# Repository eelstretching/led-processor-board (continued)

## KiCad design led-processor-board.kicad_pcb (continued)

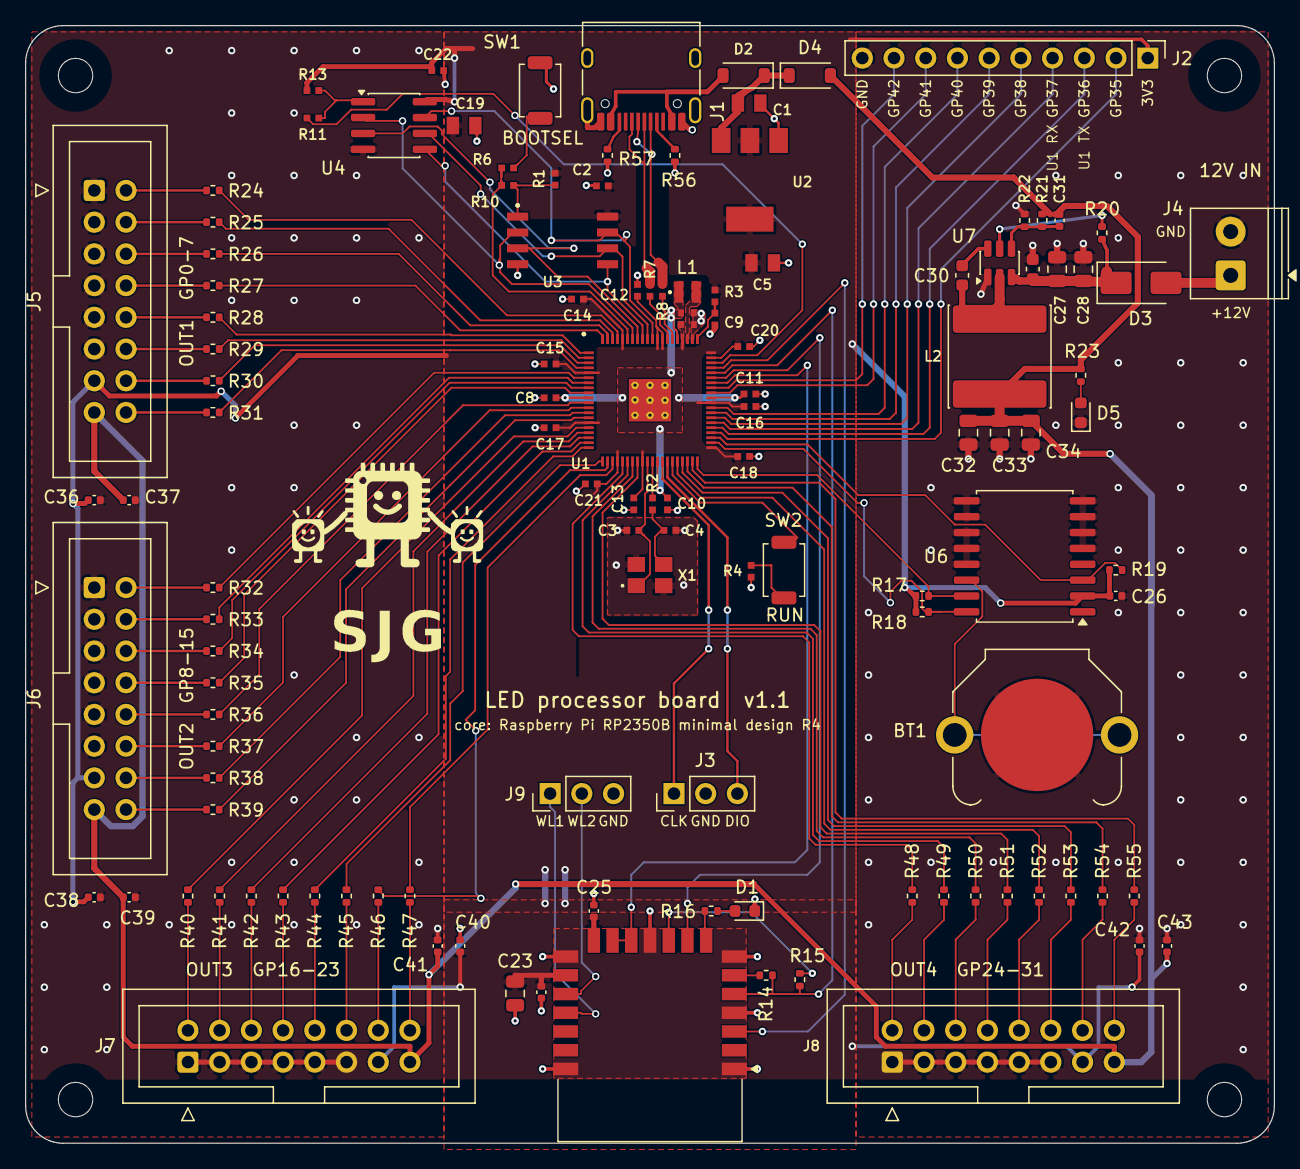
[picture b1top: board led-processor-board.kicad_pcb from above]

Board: 2 copper layers, 100.0 x 89.5 mm, 128 parts (0 on the bottom side), 124 nets.

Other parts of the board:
G1: SJG_BigBrother

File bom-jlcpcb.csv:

Comment,Designator,Footprint,LCSC,Manufacturer PN,Qty,Note
CR1220,BT1,BatteryHolder_Keystone_3001_1x12mm,,3001,1,"Not at LCSC: Keystone 3001 (Digi-Key 36-3001-ND), hand-solder"
10u,"C1,C5,C19",generic_capc2012x125,C15850,CL21A106KAYNNNE,3,
100n,"C2,C8,C10,C11,C12,C13,C14,C15,C16,C17,C18,C20,C21,C22",generic_capc1005x50,C1525,CL05B104KO5NNNC,14,
15p,"C3,C4",generic_capc1005x50,C1548,0402CG150J500NT,2,
4.7u,"C6,C7",generic_capc1005x50_wide,C23733,CL05A475MP5NRNC,2,
4.7u,C9,generic_capc1005x50,C23733,CL05A475MP5NRNC,1,
10u,C23,C_0805_2012Metric,C15850,CL21A106KAYNNNE,1,
100n,"C24,C25,C36,C37,C38,C39,C40,C41,C42,C43",C_0402_1005Metric,C1525,CL05B104KO5NNNC,10,
1u,C26,C_0402_1005Metric,C52923,CL05A105KA5NQNC,1,
10u,"C27,C28",C_0805_2012Metric,C440198,CL21A106KBYNNNE,2,
100n,"C29,C30",C_0603_1608Metric,C14663,CC0603KRX7R9BB104,2,
75p,C31,C_0402_1005Metric,C37809,0402CG750J500NT,1,
22u,"C32,C33,C34",C_0805_2012Metric,C45783,CL21A226MAQNNNE,3,
Green,"D1,D5",LED_0603_1608Metric,C72043,19-217/GHC-YR1S2/3T,2,
B5819W,"D2,D4",D_SOD-123,C8598,B5819W SL,2,
SS34,D3,D_SMA,C8678,SS34,1,
USB-C,J1,USB_C_Receptacle_HRO_TYPE-C-31-M-12,C165948,TYPE-C-31-M-12,1,
SPARE,J2,PinHeader_1x10_P2.54mm_Vertical,,1x10 2.54 mm pin header,1,Through-hole: hand-solder
SWD,J3,PinHeader_1x03_P2.54mm_Vertical,,1x3 2.54 mm pin header,1,Through-hole: hand-solder
12V IN,J4,"TerminalBlock_Phoenix_PT-1,5-2-3.5-H_1x02_P3.50mm_Horizontal",C695629,DB301V-3.5-2P-GN-S,1,Through-hole
OUT1,J5,IDC-Header_2x08_P2.54mm_Vertical,,Box header 2x08 2.54 mm,1,Through-hole: hand-solder (same shroud as the output boards)
OUT2,J6,IDC-Header_2x08_P2.54mm_Vertical,,Box header 2x08 2.54 mm,1,Through-hole: hand-solder (same shroud as the output boards)
OUT3,J7,IDC-Header_2x08_P2.54mm_Vertical,,Box header 2x08 2.54 mm,1,Through-hole: hand-solder (same shroud as the output boards)
OUT4,J8,IDC-Header_2x08_P2.54mm_Vertical,,Box header 2x08 2.54 mm,1,Through-hole: hand-solder (same shroud as the output boards)
WL_GPIO,J9,PinHeader_1x03_P2.54mm_Vertical,,1x3 2.54 mm pin header,1,Through-hole: hand-solder
3.3u,L1,abracon_aota-b201610s3r3-101-t,C42411119,AOTA-B201610S3R3-101-T,1,
15u,L2,L_Sunlord_SWPA8040S,C16853,SWPA8040S150MT,1,
1k,"R2,R4,R6",generic_resc1005x35,C11702,0402WGF1001TCE,3,
33,R3,generic_resc1005x35,C25105,0402WGF330JTCE,1,
27,"R7,R8",generic_resc1005x35,C25100,0402WGF270JTCE,2,
0,"R10,R11",generic_resc1005x35,C17168,0402WGF0000TCE,2,
10k,R13,generic_resc1005x35,C25744,0402WGF1002TCE,1,
470,R14,R_0402_1005Metric,C25117,0402WGF4700TCE,1,
10k,"R15,R17,R18,R19",R_0402_1005Metric,C25744,0402WGF1002TCE,4,
1k,"R16,R23",R_0402_1005Metric,C11702,0402WGF1001TCE,2,
510k,R20,R_0402_1005Metric,C11616,0402WGF5103TCE,1,
100k,R21,R_0402_1005Metric,C25741,0402WGF1003TCE,1,
13.3k,R22,R_0402_1005Metric,C122547,0402WGF1332TCE,1,
33,"R24,R25,R26,R27,R28,R29,R30,R31,R32,R33,R34,R35,R36,R37,R38,R39,R40,R41,R42,R43,R44,R45,R46,R47,R48,R49,R50,R51,R52,R53,R54,R55",R_0402_1005Metric,C25105,0402WGF330JTCE,32,
5.1k,"R56,R57",R_0402_1005Metric,C25905,0402WGF5101TCE,2,
TS-1088R-02526,"SW1,SW2",SW_SPST_TS-1088-xR025,C455281,TS-1088R-02526,2,
RP2350B,U1,rpi_rp2350b_vias,C42415655,RP2350B,1,
NCP1117ST33T3G,U2,onsemi_ncp1117st33t3g,C26537,NCP1117ST33T3G,1,
W25Q128JVSIQ,U3,generic_soic127p790x195-8,C97521,W25Q128JVSIQ,1,
APS6404L-3SQR-SN,U4,SOIC-8_3.9x4.9mm_P1.27mm,C5333729,APS6404L-3SQR-SN,1,
RM2,U5,RPi_RM2,,SC1169 (RMC20452T),1,Not at LCSC: buy RM2 (Raspberry Pi SC1169) and hand-solder
DS3231SN,U6,SOIC-16W_7.5x10.3mm_P1.27mm,C9866,DS3231SN#T&R,1,
TPS54202H,U7,SOT-23-6,C527684,TPS54202HDDCR,1,
12MHz,X1,generic_xtalcc320x250x80-4,C20625731,ABM8-272-T3,1,

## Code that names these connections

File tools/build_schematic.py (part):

"""Build the LED processor board schematic from the RP2350B-RM2 reference.

Root sheet: the reference (RP2350B, flash, PSRAM, RM2, USB, crystal, buttons) with the
J2/J3 single-row headers replaced by the DS3231 RTC, a spare-GPIO header and an SWD
header. GPIO0-31 become global labels and go to the Outputs sheet (four 16-pin ribbon
shrouds, pinout as the output boards). Power sheet: 12 V in -> TPS54202H buck -> +5 V
(ribbons) -> B5819W -> VSYS (existing NCP1117 3.3 V regulator).
"""
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
walk(ref)
for e in sx.findall(ref, 'text'):
    if e[1].startswith('VSYS is also J3 pin 2'):
        e[1] = ('VSYS comes from the 12 V input: buck to +5V, then\n'
                'D4 (Power sheet). D2 keeps that 5 V off the USB port;\n'
                'USB alone runs it through D2 (no +5V on ribbons).')

# 4. new root content: RTC, spare GPIO header, SWD header
sh = root
U6 = sh.symbol('Timer_RTC:DS3231M', SYM['Timer_RTC:DS3231M'], 'U6', 'DS3231SN', (370.84, 142.24),
               fields=part('DS3231SN#T&R', 'C9866', 'Analog Devices (Maxim)',
                           'RTC with TCXO and crystal, I2C, SOIC-16W (same as universal-strip-controller U9)',
                           'Package_SO:SOIC-16W_7.5x10.3mm_P1.27mm'),
               ref_at=(374.65, 128.27), val_at=(374.65, 130.81))
sh.wire(U6[16], (350.52, U6[16][1])); sh.label('GPIO33', (350.52, U6[16][1]), 180)
sh.wire(U6[15], (350.52, U6[15][1])); sh.label('GPIO32', (350.52, U6[15][1]), 180)
sh.nc(U6[4]); sh.nc(U6[1])
sh.wire(U6[3], (391.16, U6[3][1])); sh.label('GPIO34', (391.16, U6[3][1]), 0)
sh.wire(U6[2], (U6[2][0], 127.0)); pwr(sh, '+3V3', (U6[2][0], 127.0))
gnd(sh, U6[13])
# battery: VBAT up and over to BT1
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C26 = C(sh, 'C26', '1u', (345.44, 124.46), ref_at=(347.98, 123.19), val_at=(347.98, 125.73))
pwr(sh, '+3V3', C26[1]); gnd(sh, C26[2])
# pull-ups on SDA, SCL, INT
for k, (refd, net) in enumerate([('R17', 'GPIO32'), ('R18', 'GPIO33'), ('R19', 'GPIO34')]):
    x = 345.44 + 7.62 * k
    rr = R(sh, refd, '10k', (x, 163.83), ref_at=(x + 1.905, 162.56), val_at=(x + 1.905, 165.1))
    pwr(sh, '+3V3', rr[1])
    sh.wire(rr[2], (x, 172.72)); sh.label(net, (x, 172.72), 270)
sh.text('RTC: the DS3231 circuit from universal-strip-controller (U9), on I2C0:\n'
        'SDA = GPIO32, SCL = GPIO33, INT/SQW = GPIO34 (open drain, pulled up).\n'
        '32KHZ and RST unused. CR1220 in a Keystone 3001 holder.', (335.28, 114.3))
# spare GPIO header J2
J2 = sh.symbol('Connector_Generic:Conn_01x10', SYM['Connector_Generic:Conn_01x10'], 'J2', 'SPARE',
               (403.86, 182.88),
               fields=part('1x10 2.54 mm pin header', '', '', 'Spare GPIO35-42, 3V3, GND. Through-hole: hand-solder',
                           'Connector_PinHeader_2.54mm:PinHeader_1x10_P2.54mm_Vertical'),
               ref_at=(400.05, 166.37), val_at=(403.86, 166.37))
sh.wire(J2[1], (393.7, J2[1][1])); pwr(sh, '+3V3', (393.7, J2[1][1]))
for n, net in zip(range(2, 10), ['GPIO35', 'GPIO36', 'GPIO37', 'GPIO38', 'GPIO39', 'GPIO40_ADC0',
                                 'GPIO41_ADC1', 'GPIO42_ADC2']):
    sh.wire(J2[n], (388.62, J2[n][1])); sh.label(net, (388.62, J2[n][1]), 180)
sh.wire(J2[10], (393.7, J2[10][1])); gnd(sh, (393.7, J2[10][1]))
# SWD header J3 (Pico debug pin order)
J3 = sh.symbol('Connector_Generic:Conn_01x03', SYM['Connector_Generic:Conn_01x03'], 'J3', 'SWD',
               (403.86, 157.48),
               fields=part('1x3 2.54 mm pin header', '', '', 'SWD debug: SWCLK, GND, SWD (Pico order). Through-hole: hand-solder',
                           'Connector_PinHeader_2.54mm:PinHeader_1x03_P2.54mm_Vertical'),
               ref_at=(400.05, 149.86), val_at=(403.86, 149.86))
sh.wire(J3[1], (388.62, J3[1][1])); sh.label('SWCLK', (388.62, J3[1][1]), 180)
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pwr_n[0] += 1
sh.symbol('RPI - Power:GND', SYM['RPI - Power:GND'], '#PWR%d' % pwr_n[0], 'GND', (393.7, J3[2][1]), rot=270,
          power=True, in_bom=False, val_at=(389.89, J3[2][1] - 1.27), hide_value=True)
sh.wire(J3[3], (388.62, J3[3][1])); sh.label('SWD', (388.62, J3[3][1]), 180)
sh.text('J2: spare GPIO35-42. UART1 TX/RX = GPIO36/37,\n'
        'GPIO40-42 = ADC0-2. J3: SWD in a Pico\'s debug pin order.\n'
        'GPIO0-31 go to the four output shrouds (Outputs sheet).\n'
        'GPIO43-47 are the RM2 and the PSRAM.', (335.28, 213.36))

# 4b. USB-C receptacle in place of Pi's micro-B
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    y = oy + 2.54 + 2.54 * i
    sh.wire((ox, y), (ox - 5.08, y)); sh.label('GPIO%d' % i, (ox - 5.08, y), 180)
    sh.wire((ox + ow, y), (ox + ow + 5.08, y)); sh.label('GPIO%d' % (16 + i), (ox + ow + 5.08, y), 0)
sh.text('GPIO0-31 to the four output shrouds', (ox - 5.08, oy - 3.81))
sh.text('12 V in, 5 V buck', (355.6, 63.5), size=2.54)

# ======================================================================================
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D3 = sh.symbol('Device:D_Schottky', SYM['Device:D_Schottky'], 'D3', 'SS34', (44.45, 76.2), rot=180,
               fields=part('SS34', 'C8678', 'MDD', 'Schottky 40 V 3 A, reverse-polarity protection', 'Diode_SMD:D_SMA'),
               ref_at=(41.91, 71.12), val_at=(41.91, 73.66))
sh.wire(J4[1], D3[2]); sh.label('VIN_RAW', (33.02, 76.2), 0)
# +12V bus with taps
taps12 = [D3[1][0], 50.8, 53.34, 58.42, 66.04, 73.66, 81.28, 91.44]
for a, b in zip(taps12, taps12[1:]):
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
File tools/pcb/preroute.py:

# hand routing for the buck (exec'd by build_pcb.py after placement)
def trk(net_name, pts, w, layer=pcbnew.F_Cu):
    for (x0, y0), (x1, y1) in zip(pts, pts[1:]):
        t = pcbnew.PCB_TRACK(b)
        t.SetStart(V(x0, y0)); t.SetEnd(V(x1, y1))
        t.SetWidth(mm(w)); t.SetLayer(layer)
        t.SetNet(net(net_name))
        b.Add(t)


def via(net_name, x, y, d=0.6, drill=0.3):
    v = pcbnew.PCB_VIA(b)
    v.SetPosition(V(x, y)); v.SetWidth(mm(d)); v.SetDrill(mm(drill))
    v.SetNet(net(net_name))
    b.Add(v)


# 12 V in: J4 -> D3 -> input caps -> VIN
trk('/Power/VIN_RAW', [(146.5, 90.0), (145.9, 90.6), (141.32, 90.6)], 0.8)
trk('+12V', [(137.32, 90.6), (134.7, 90.45), (132.6, 90.45), (130.65, 90.45)], 0.8)
trk('+12V', [(130.65, 90.45), (129.6, 90.45), (128.95, 90.138)], 0.6)
# input caps' GND straight down to the bottom plane
for x, y in ((130.65, 87.6), (132.6, 87.45), (134.7, 87.45)):
    trk('GND', [(x, y), (x, y + 1.0)], 0.5)
    via('GND', x, y)
# SW node: pin 2 straight down into L2, boot cap alongside
trk('/Power/SW', [(128.0, 90.138), (128.0, 93.0)], 0.8)
trk('/Power/SW', [(125.0, 90.775), (125.0, 93.0)], 0.5)
trk('Net-(U7-BOOT)', [(127.05, 87.862), (126.3, 87.862), (125.0, 89.162), (125.0, 89.225)], 0.3)
# U7 GND: the boot cap and SW wall it in on top, so it drops to the plane
trk('GND', [(127.05, 90.138), (126.5, 91.5)], 0.4)
via('GND', 126.5, 91.5)
# EN pull-up from the 12 V riser; EN hops under the FB parts on B.Cu
trk('+12V', [(136.2, 87.11), (136.6, 88.0), (136.6, 89.9)], 0.3)
trk('Net-(U7-EN)', [(136.2, 86.09), (136.2, 85.2)], 0.25)
via('Net-(U7-EN)', 136.2, 85.2)
trk('Net-(U7-EN)', [(136.2, 85.2), (128.0, 86.3)], 0.25, pcbnew.B_Cu)
via('Net-(U7-EN)', 128.0, 86.3)
trk('Net-(U7-EN)', [(128.0, 86.3), (128.0, 87.862)], 0.25)
# FB divider right above FB
trk('/Power/FB', [(128.95, 87.862), (128.95, 86.6), (129.44, 86.11), (130.0, 86.11), (131.4, 86.11), (132.8, 86.08)], 0.25)
trk('+5V', [(131.4, 85.09), (132.8, 85.12)], 0.25)
trk('GND', [(130.0, 85.09), (129.3, 84.4)], 0.3)
via('GND', 129.3, 84.4)
# output: L2 into the three 22u, their GND to the plane
trk('+5V', [(128.0, 100.4), (128.0, 101.65)], 0.8)
trk('+5V', [(125.5, 101.65), (130.5, 101.65)], 0.8)
for x in (125.5, 128.0, 130.5):
    trk('GND', [(x, 103.55), (x, 104.7)], 0.5)
    via('GND', x, 104.7)

# USB-C, left to right: B5 CC2, A8, B6 D+, A7 D-, A6 D+, B7 D-, A5 CC1, B8, A4 VBUS (0.5 mm pitch).
# A6/B7 carry the pair down to R7/R8; B6 joins D+ round the A7 via, and A7 hops to D- on B.Cu
# (above Pi's GPIO47 trace, which runs across under here on B.Cu).
PY = 77.695
trk('/USB_D+', [(99.55, PY), (99.55, 89.25), (99.725, 89.425)], 0.15)
trk('/USB_D-', [(100.05, PY), (100.05, 79.9), (100.15, 80.3), (100.05, 80.7), (100.05, 88.35), (100.675, 88.975)], 0.15)
trk('/USB_D+', [(98.55, PY), (98.55, 78.7), (98.35, 78.9), (98.35, 79.9), (99.55, 81.1)], 0.15)
trk('/USB_D-', [(99.05, PY), (99.05, 78.42), (98.95, 79.3)], 0.15)
via('/USB_D-', 98.95, 79.3)
trk('/USB_D-', [(98.95, 79.3), (100.15, 80.3)], 0.15, pcbnew.B_Cu)
via('/USB_D-', 100.15, 80.3)
# CC pull-downs
trk('Net-(J1-CC1)', [(100.55, PY), (100.55, 78.42), (101.0, 78.87), (102.0, 79.89)], 0.2)
trk('Net-(J1-CC2)', [(97.55, PY), (97.55, 78.42), (97.1, 78.87), (96.6, 79.89)], 0.2)
for x in (102.0, 96.6):
    trk('GND', [(x, 80.91), (x, 81.8)], 0.3)
    via('GND', x, 81.8)
# VBUS: both VBUS pads up past the locating pegs, across under the receptacle, then to D2;
# D2/D4 feed VSYS at C1 and U2
trk('VBUS', [(96.85, PY), (96.95, 77.0), (97.25, 76.45), (97.25, 75.3), (101.35, 75.3)], 0.3)
trk('VBUS', [(101.75, PY), (101.65, 77.0), (101.35, 76.45), (101.35, 75.3)], 0.3)
trk('VBUS', [(101.35, 75.3), (104.6, 75.3), (105.85, 74.05)], 0.4)
trk('VSYS', [(109.15, 74.0), (111.15, 74.0)], 0.5)
trk('VSYS', [(109.15, 74.0), (108.2, 74.95), (107.04, 75.6)], 0.5)
trk('VSYS', [(107.04, 76.9), (105.7, 78.2)], 0.5)

# ---------------------------------------------------------------- OUT4 bus (GPIO24-31) and SWD
# Pi's escapes off the bottom of U1, then one 0.3 mm-pitch bus down a channel right of SW2
# and across to R48-R55. GPIO24-27 escape left and U-turn under X1; GPIO28-31 escape right.
C = 0.5                                   # 45-degree chamfer
CH = {k: 112.75 + 0.3 * (k - 24) for k in range(24, 32)}      # channel x
HB = {k: 133.5 + 0.3 * (31 - k) for k in range(24, 32)}       # bottom run y (GPIO31 on top)
HL = {27: 118.0, 26: 118.3, 25: 118.6, 24: 118.9}             # left group's crossing y
RX = {k: 121.0 + 2.54 * (k - 24) for k in range(24, 32)}      # R48-R55 x
RY = 139.19                                                   # R48-R55 pad 2 y
LEFT = {24: ((97.8, 105.9), 93.8), 25: ((98.2, 106.0), 94.6),
        26: ((98.6, 106.1), 95.4), 27: ((99.0, 106.2), 96.2)}
for k, ((px, py), vx) in LEFT.items():
    dy = py + (px - vx)                   # 45-degree run down to the vertical
    trk('/GPIO%d' % k, [(px, 104.9), (px, py), (vx, dy), (vx, HL[k] - C), (vx + C, HL[k]),
                        (CH[k] - C, HL[k]), (CH[k], HL[k] + C)], 0.15)
RIGHT = {28: [(102.2, 105.9), (104.1, 107.8), (109.8, 107.8)],
         29: [(102.6, 105.79), (104.21, 107.4), (110.6, 107.4)],
         30: [(103.0, 105.7), (104.3, 107.0), (111.41, 107.0)],
         31: [(103.4, 105.6), (104.4, 106.6), (113.55, 106.6)]}
for k, pts in RIGHT.items():
    ex, ey = pts[-1]
    trk('/GPIO%d' % k, [(pts[0][0], 104.9)] + pts + [(CH[k], ey + CH[k] - ex)], 0.15)
for k in range(24, 32):
    top = HL[k] + C if k in HL else RIGHT[k][-1][1] + CH[k] - RIGHT[k][-1][0]
    trk('/GPIO%d' % k, [(CH[k], top), (CH[k], HB[k] - C), (CH[k] + C, HB[k]),
                        (RX[k] - C, HB[k]), (RX[k], HB[k] + C), (RX[k], RY)], 0.15)
# SWD header J3 (vertical, pin 1 = SWCLK at the top) right under the escapes
trk('/SWCLK', [(101.0, 104.9), (101.0, 106.3), (104.7, 110.0), (104.7, 111.8)], 0.15)
trk('/SWD', [(101.4, 104.9), (101.4, 106.19), (106.2, 110.99), (106.2, 115.9), (105.22, 116.88), (104.7, 116.88)], 0.15)

# ---------------------------------------------------------------- RM2 bus (GPIO43-46)
# Pi's escapes run up-right off U1; drop each to B.Cu on its diagonal, run down the right of
# the core and come back in to the RM2 (U5) pads and Pi's R14/R15 on GPIO45.
RM2 = {43: [(108.0, 98.0), (111.8, 98.0), (112.6, 97.2)],
       44: [(108.0, 97.6), (111.0, 97.6), (113.6, 95.0)],
       45: [(108.0, 97.2), (110.19, 97.2), (114.6, 92.79)],
       46: [(108.0, 96.8), (109.4, 96.8), (115.6, 90.6)]}
NM = {43: '/GPIO43_ADC3', 44: '/GPIO44_ADC4', 45: '/GPIO45_ADC5', 46: '/GPIO46_ADC6'}
for k, pts in RM2.items():
    trk(NM[k], pts, 0.15)
    via(NM[k], *pts[-1])
B = pcbnew.B_Cu
trk(NM[43], [(112.6, 97.2), (112.6, 136.0), (111.6, 137.0), (99.5, 137.0), (98.5, 138.0), (98.5, 140.6)], 0.15, B)
via(NM[43], 98.5, 140.6)
trk(NM[43], [(98.5, 140.6), (98.5, 141.5)], 0.15)
trk(NM[44], [(113.6, 95.0), (113.6, 137.0), (112.6, 138.0), (104.0, 138.0), (103.0, 139.0), (103.0, 140.3)], 0.15, B)
via(NM[44], 103.0, 140.3)
trk(NM[44], [(103.0, 140.3), (103.0, 141.5)], 0.15)
trk(NM[45], [(114.6, 92.79), (114.6, 146.45), (113.5, 147.55)], 0.15, B)
via(NM[45], 113.5, 147.55)
trk(NM[45], [(113.5, 147.55), (108.0, 147.55)], 0.15)
trk(NM[45], [(109.81, 147.55), (109.81, 146.05)], 0.15)
trk(NM[45], [(112.0, 147.55), (112.0, 146.91)], 0.15)
trk(NM[46], [(115.6, 90.6), (115.6, 147.6), (112.65, 150.55), (109.0, 150.55)], 0.15, B)
via(NM[46], 109.0, 150.55)
trk(NM[46], [(109.0, 150.55), (108.0, 150.55)], 0.15)

# ---------------------------------------------------------------- +3V3 the router missed
# J7 pin 13: between the shroud rows on B.Cu to the RM2-end 3V3 pour
trk('+3V3', [(78.24, 147.2), (79.51, 145.93), (84.6, 145.93)], 0.3, B)
via('+3V3', 84.6, 145.93)
# RTC side (R17-R19, U6) is walled off from the core pour by the OUT4 and RM2 buses:
# feed it from J2 pin 1 on B.Cu
trk('+3V3', [(121.29, 115.67), (120.4, 115.0)], 0.3)
via('+3V3', 120.4, 115.0)
trk('+3V3', [(120.4, 115.0), (120.4, 86.0), (118.5, 86.0)], 0.3, B)
trk('+3V3', [(118.5, 86.0), (116.0, 86.0)], 0.3)

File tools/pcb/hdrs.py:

#!/usr/bin/env python3
"""Put J9 (RM2 WL_GPIO1/2) and J3 (SWD) side by side in the open area under the board name.
Replaces wlhdr.py's spot beside the RM2 (C23/C24 stay where Pi had them). Rips the SWD tracks;
route.sh routes SWCLK/SWD and WL_GPIO1/2.

usage: hdrs.py in.kicad_pcb out.kicad_pcb       (in = the board before wlhdr.py)
"""
import sys
import pcbnew

IN, OUT = sys.argv[1:3]
mm, M = pcbnew.FromMM, pcbnew.ToMM
b = pcbnew.LoadBoard(IN)
SYM_UUID = 'da6c4e4c-3e09-48ab-bdbc-08436853f8dc'      # J9 in led-processor-board.kicad_sch
Y = 131.5                                              # header row
J9_X, J3_X = 92.0, 101.92                              # pin 1 of each, pins run +x


def V(x, y):
    return pcbnew.VECTOR2I(mm(x), mm(y))


def net(name):
    n = b.FindNet(name)
    if n is None:
        n = pcbnew.NETINFO_ITEM(b, name)
        b.Add(n)
    return n


for t in list(b.GetTracks()):
    if t.GetNetname() in ('/SWCLK', '/SWD'):
        b.Delete(t)

f = b.FindFootprintByReference('J3')
f.SetOrientationDegrees(90)
f.SetPosition(V(J3_X, Y))

lib = '/usr/share/kicad/footprints/Connector_PinHeader_2.54mm.pretty'
f = pcbnew.FootprintLoad(lib, 'PinHeader_1x03_P2.54mm_Vertical')
f.SetFPIDAsString('Connector_PinHeader_2.54mm:PinHeader_1x03_P2.54mm_Vertical')
f.SetReference('J9'); f.SetValue('WL_GPIO')
f.SetPath(pcbnew.KIID_PATH('/' + SYM_UUID))
f.SetSheetname('led-processor-board'); f.SetSheetfile('led-processor-board.kicad_sch')
b.Add(f)
f.SetOrientationDegrees(90)
f.SetPosition(V(J9_X, Y))
f.Value().SetVisible(False)
for p in f.Pads():
    p.SetNet(net({'1': '/WL_GPIO1', '2': '/WL_GPIO2', '3': 'GND'}[p.GetNumber()]))
for p in b.FindFootprintByReference('U5').Pads():
    if p.GetNumber() in ('17', '18'):
        p.SetNet(net('/WL_GPIO2' if p.GetNumber() == '17' else '/WL_GPIO1'))

# pin labels under each header (J3's old ones sat beside it)
for d in list(b.GetDrawings()):
    if d.GetClass() == 'PCB_TEXT' and d.GetText() in ('CLK', 'GND', 'DIO') \
            and abs(M(d.GetPosition().x) - 106.9) < 0.05:
        b.Delete(d)
for x0, labs in ((J9_X, ('WL1', 'WL2', 'GND')), (J3_X, ('CLK', 'GND', 'DIO'))):
    for i, lab in enumerate(labs):
        t = pcbnew.PCB_TEXT(b)
        t.SetText(lab); t.SetLayer(pcbnew.F_SilkS)
        t.SetTextSize(V(0.8, 0.8)); t.SetTextThickness(mm(0.12))
        t.SetPosition(V(x0 + 2.54 * i, Y + 2.2))
        b.Add(t)

b.BuildConnectivity()
pcbnew.ZONE_FILLER(b).Fill(b.Zones())
pcbnew.SaveBoard(OUT, b, True)
